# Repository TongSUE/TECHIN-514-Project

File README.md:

# TECHIN-514-Project : The Reality Color Dropper

## 1. Project Overview

**What it does:**
This project brings the digital "eyedropper" tool into real life. It consists of a pen-shaped device that scans the color of physical objects and a desktop station that displays the color data and the confidence level of the match. It helps designers capture colors from the real world instantly.

---

## 2. The Sensor Device (The Pen)

**Description:**
This is a handheld tool shaped like a marker pen. It utilizes a custom split-PCB architecture to fit the slim form factor. When the user finds a color, they press the button; the device reads the RGB value while blocking outside light and sends the data wirelessly to the base station.

**Key Components & Part Numbers:**

* **Controller: Seeed Studio XIAO ESP32C3**
    This thumb-sized microcontroller is selected for its compact footprint and built-in ESP-NOW capabilities. It fits perfectly inside the pen shaft.

* **Sensor Architecture: Split Custom PCB**
    To accommodate the pen's geometry, the circuit is split into two boards connected by a **1x4 Pin Header**:
    1.  **Main Board:** Vertically mounted inside the pen. Houses the MCU, battery pads, and switch.
    2.  **Sensor Tip:** A circular PCB mounted horizontally at the tip. Houses the **TCS34725 Sensor** and **LEDs** to ensure the sensor faces the paper perpendicularly.

* **Input: Tactile Button**
    Acts as a "shutter" trigger.

* **Power: Li-Po Battery (AAA size)**
    A cylindrical/prismatic lithium battery that connects to the motherboard via a battery holder.

* **Power Switch: Slide Switch**
    A side-mounted switch to cut off power completely.

---

## 3. The Display Device (The Base)

**Description:**
This is a desktop base that receives the color data. It features an OLED screen for data readout, a stepper motor gauge for visual feedback on accuracy, and a large LED for color reproduction.

**Key Components & Part Numbers:**

* **Controller: Seeed Studio XIAO ESP32C3**
    The base station uses the exact same controller as the pen. This unified architecture simplifies the codebase and BOM.

* **Display: 0.96" OLED Screen (SSD1306 Driver)**
    Displays the Hex/RGB codes via I2C interface.

* **Color Output: RGB LED**
    A programmable NeoPixel LED to visually visually recreate the scanned color.

* **Motor: x27_168 Stepper Motor**
    Indicates the "Confidence Level" (Euclidean distance) of the color match.

* **Power: 18650 Li-Ion Battery**
    Provides long-lasting power, boosted to 5V for the motor and LEDs.

---

## 4. System Logic & Communication

**Communication Method:**
The devices talk to each other using **ESP-NOW**.
* It is a peer-to-peer protocol (low latency).
* It does not require a router or Wi-Fi pairing.

**Workflow:**

1.  **Trigger:** User clicks the pen button.
2.  **Sensing:** The TCS34725 sensor (on the Daughterboard) reads the Raw RGB data.
3.  **Sending:** The Pen (XIAO ESP32C3) processes the data and sends it via ESP-NOW.
4.  **Receiving:** The Base (XIAO ESP32C3) receives the packet.
5.  **Processing (DSP/ML):** The Base calculates the **Euclidean Distance** between the scanned color and a stored color library (KNN algorithm).
6.  **Output:**
    * The **OLED** shows the color code.
    * The **Neopixel LED** lights up in that color.
    * The **Stepper Motor** moves the needle to show the confidence level.

---

# Electrical Schematics & PCB Layout

## Custom PCB Design
The pen utilizes a custom **Split-PCB Design** to manage the directional requirements of the sensor.

The split-PCB architecture is implemented to allow the sensor to sit perpendicular to the scanning surface for accurate readings, while the main controller fits vertically within the narrow pen shaft.

* **Connection:** The Main Board and Sensor Tip are linked via a flexible **1x5 Connector** carrying 3.3V, GND, SDA, SCL, and LED Control.
* **Power:** The battery connects to the tail of the Main Board via a **1x2 Connector**.

### **Custom PCB Screenshots**
- Sensing - Sensor Tip

- Sensing - Main Board

- Display

## Circuit Schematics

### **Sensing Device Schematic**
- Sensor Tip

- Main Board

### **Display Device Schematic**

---

# BOM

- [Sensing - Sensor Tip BOM](./schematics/Sensing_v3/sensor%20tip/sensor%20tip.csv)
- [Sensing - Main Board BOM](./schematics/Sensing_v2/sensor%20main%20board.csv)
- [Display BOM](./schematics/Display_v2/Display_v2.csv)

---

# Battery Estimate
- [Simple Power Model (Google Doc)](https://docs.google.com/spreadsheets/d/19ngwSyrM9dyAIHHAB65ps8SqUUKRAjS5MIs19pbbb7s/edit?usp=sharing)

---

# Enclosure Design
- [Enclosure Design](./enclosure/)

### Sensing Device

### Display Device

---

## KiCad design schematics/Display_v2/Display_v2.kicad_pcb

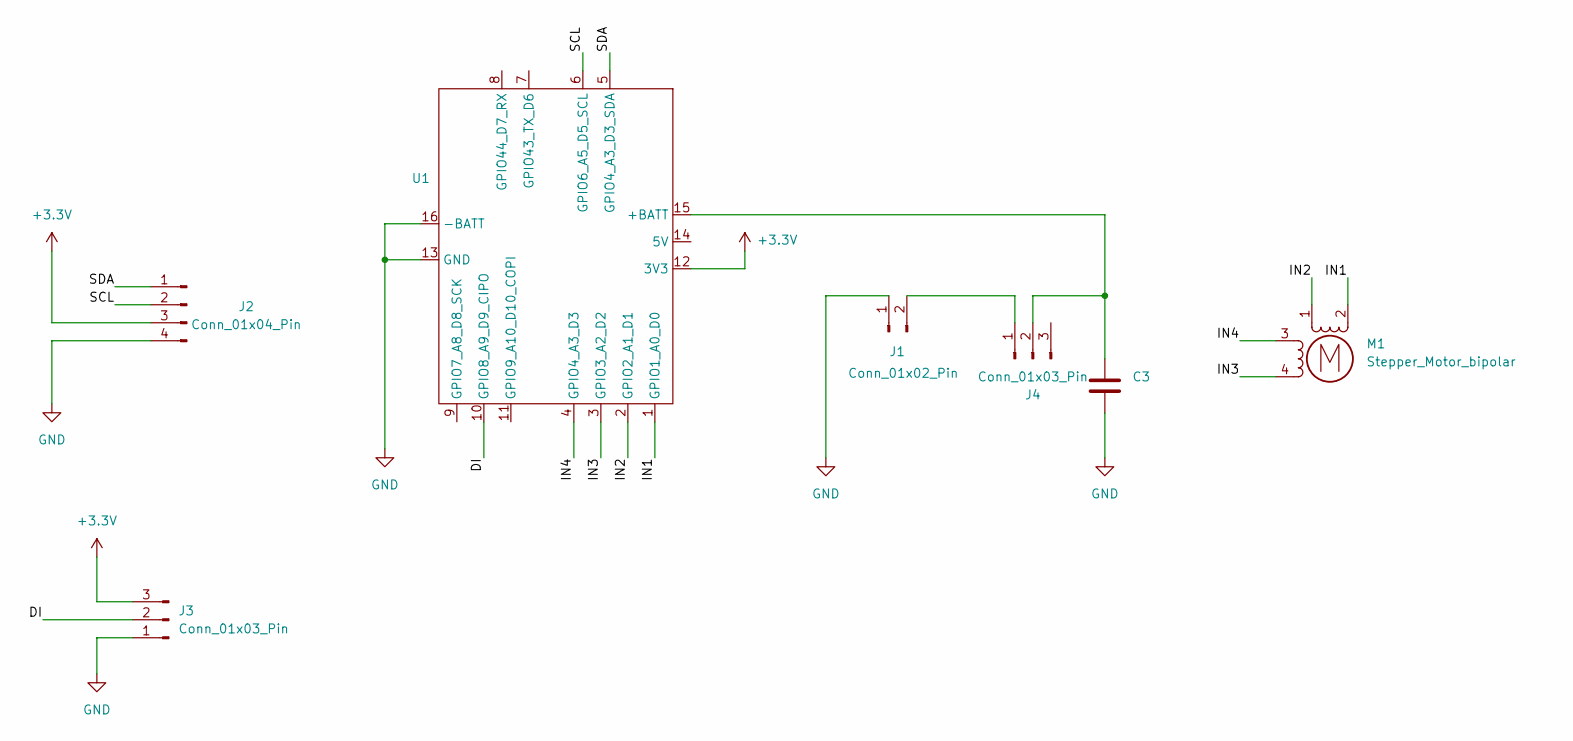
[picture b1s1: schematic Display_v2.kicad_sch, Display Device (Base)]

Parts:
C3: 22uF; C_0603_1608Metric_Pad1.08x0.95mm_HandSolder
J1: Conn_01x02_Pin; PinSocket_1x02_P2.54mm_Vertical
J2: Conn_01x04_Pin; PinSocket_1x04_P2.54mm_Vertical
J3, J4: Conn_01x03_Pin; PinSocket_1x03_P2.54mm_Vertical
M1: Stepper_Motor_bipolar; x27_stepper_two_holes
U1: XIAO_ESP32

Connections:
+3.3V: J2.3, J3.3, U1.12 (3V3)
/DI: J3.2, U1.10 (GPIO8_A9_D9_CIPO)
/IN1: M1.2 (-), U1.1 (GPIO1_A0_D0)
/IN2: M1.1, U1.2 (GPIO2_A1_D1)
/IN3: M1.4, U1.3 (GPIO3_A2_D2)
/IN4: M1.3, U1.4 (GPIO4_A3_D3)
/SCL: J2.2, U1.6 (GPIO6_A5_D5_SCL)
/SDA: J2.1, U1.5 (GPIO4_A3_D3_SDA)
GND: C3.2, J1.1, J2.4, J3.1, U1.13 (GND), U1.16 (-BATT)
unnamed: J1.2, J4.1
unnamed: C3.1, J4.2, U1.15 (+BATT)

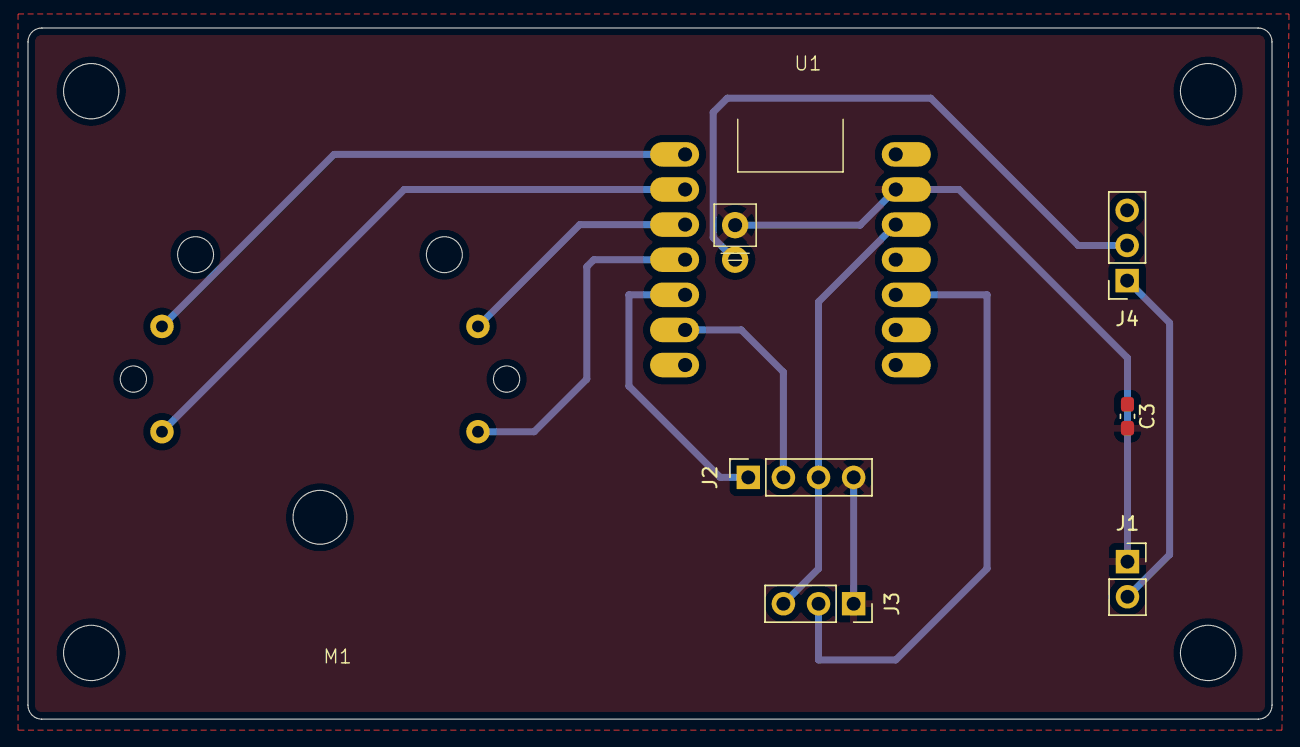
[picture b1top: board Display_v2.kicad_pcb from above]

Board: 2 copper layers, 90.0 x 50.0 mm, 7 parts (0 on the bottom side), 11 nets.

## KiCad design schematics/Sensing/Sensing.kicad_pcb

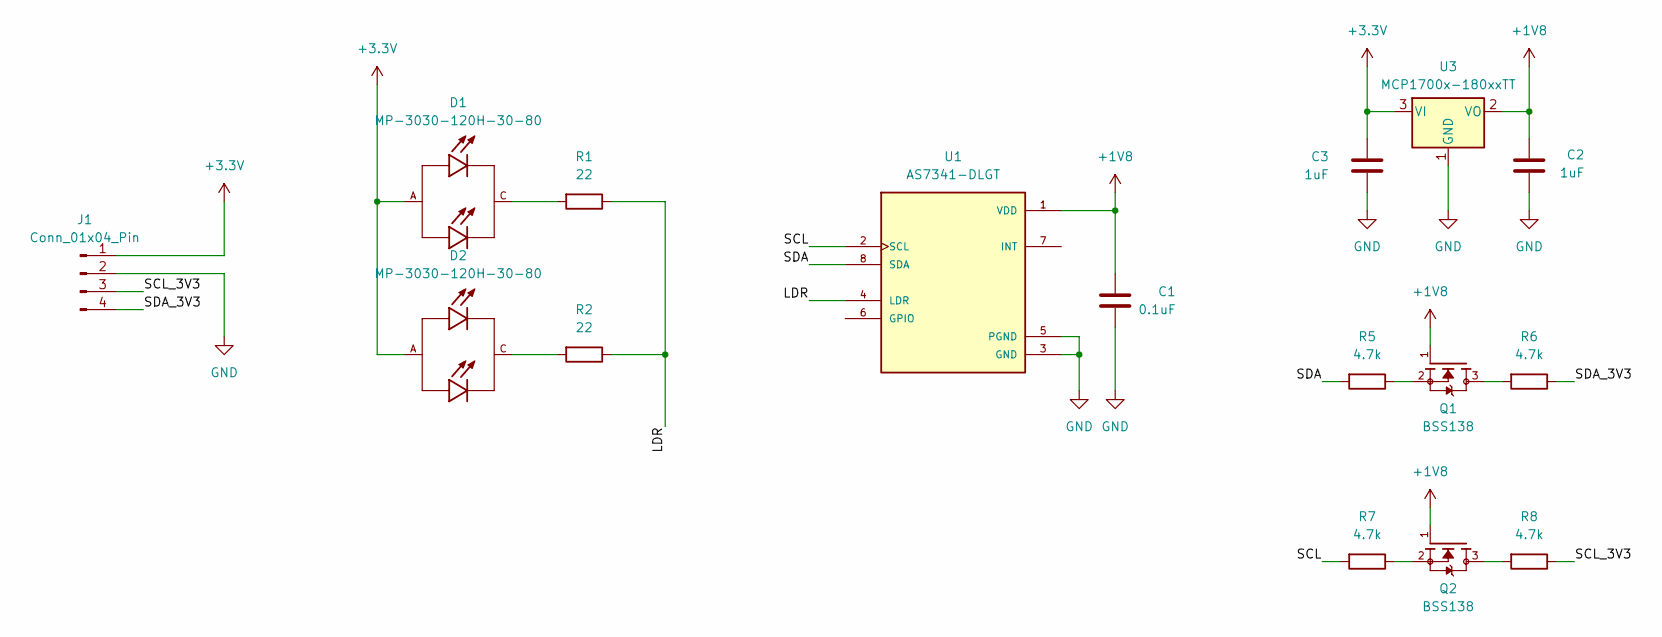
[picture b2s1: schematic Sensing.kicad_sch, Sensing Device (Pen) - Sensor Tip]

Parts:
C1: 0.1uF; C_0603_1608Metric_Pad1.08x0.95mm_HandSolder
C2, C3: 1uF; C_0603_1608Metric_Pad1.08x0.95mm_HandSolder
D1, D2: MP-3030-120H-30-80; LED_MP-3030-120H-30-80; PARTREV Rev 03
J1: Conn_01x04_Pin; PinSocket_1x04_P2.54mm_Vertical
Q1, Q2: BSS138; SOT-23_3L_ONS; PARTREV 30 Jan 2018
R1, R2: 22; R_0603_1608Metric_Pad0.98x0.95mm_HandSolder
R5, R6, R7, R8: 4.7k; R_0603_1608Metric_Pad0.98x0.95mm_HandSolder
U1: AS7341-DLGT; SON8_AS7341-DLGM_AMS; PARTREV V3
U3: MCP1700x-180xxTT; SOT-23

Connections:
+1V8: C1.1, C2.1, Q1.1, Q2.1, U1.1 (VDD), U3.2 (VO)
+3.3V: C3.1, D1.A, D2.A, J1.1, U3.3 (VI)
/LDR: R1.1, R2.1, U1.4 (LDR)
/SCL: R7.2, U1.2 (SCL)
/SCL_3V3: J1.3, R8.1
/SDA: R5.2, U1.8 (SDA)
/SDA_3V3: J1.4, R6.1
GND: C1.2, C2.2, C3.2, J1.2, U1.3 (GND), U1.5 (PGND), U3.1 (GND)
unnamed: D1.C, R1.2
unnamed: D2.C, R2.2
unnamed: Q1.2, R5.1
unnamed: Q1.3, R6.2
unnamed: Q2.2, R7.1
unnamed: Q2.3, R8.2

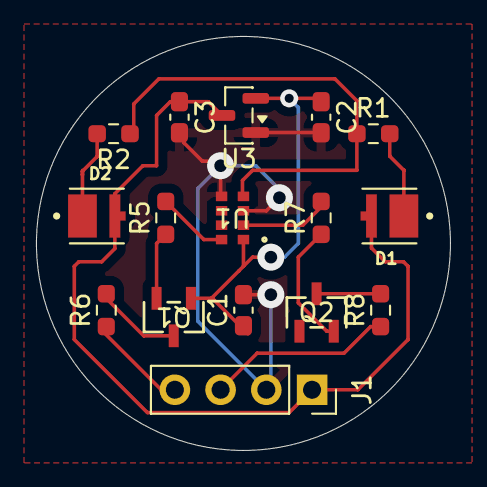
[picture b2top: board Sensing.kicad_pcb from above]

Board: 2 copper layers, 23.0 x 23.0 mm, 16 parts (0 on the bottom side), 14 nets.

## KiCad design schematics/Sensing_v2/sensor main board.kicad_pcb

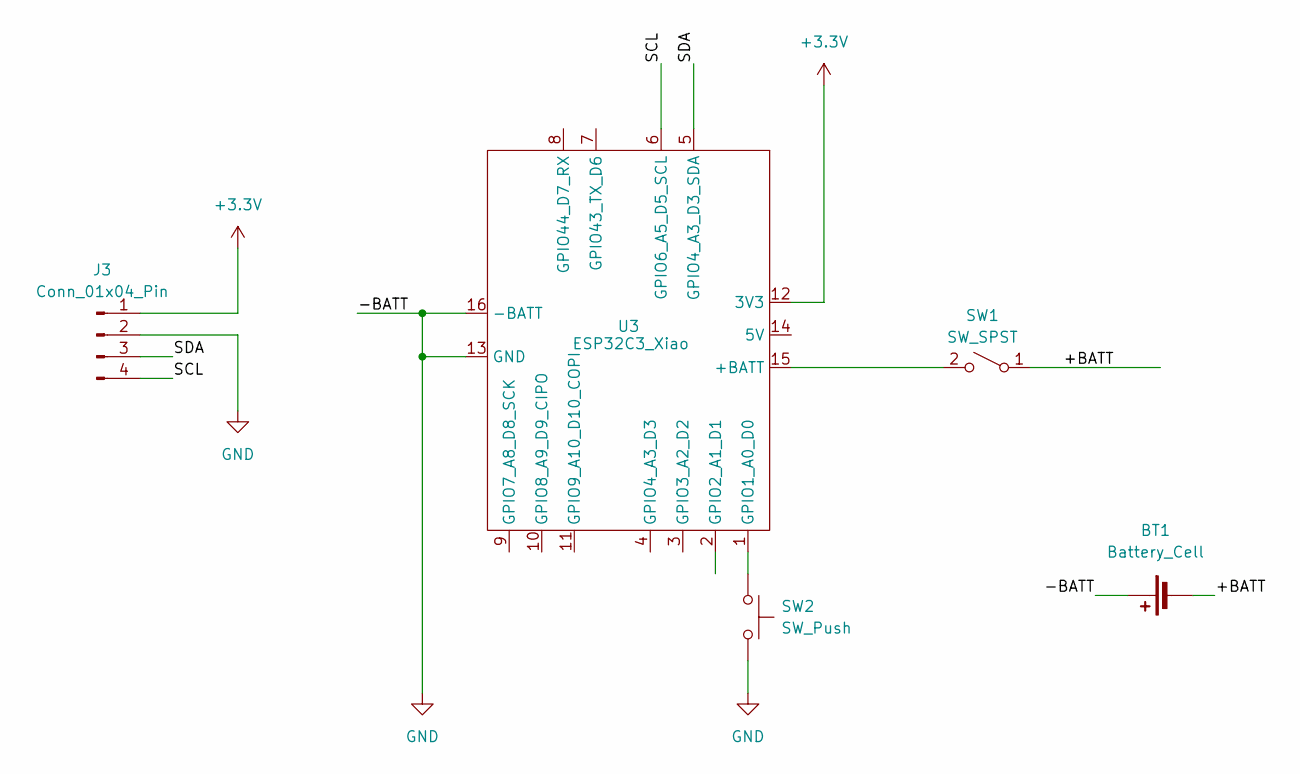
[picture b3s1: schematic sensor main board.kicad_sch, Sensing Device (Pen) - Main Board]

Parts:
BT1: Battery_Cell; BatteryHolder_Keystone_2466_1xAAA
J3: Conn_01x04_Pin; PinSocket_1x04_P2.54mm_Vertical
SW1: SW_SPST; PinSocket_1x02_P2.54mm_Vertical
SW2: SW_Push; SW_MEC_5GSH9
U3: ESP32C3_Xiao; XIAO_ESP32

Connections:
+3.3V: J3.1, U3.12 (3V3)
/+BATT: BT1.2 (-), SW1.1 (A)
/SCL: J3.4, U3.6 (GPIO6_A5_D5_SCL)
/SDA: J3.3, U3.5 (GPIO4_A3_D3_SDA)
GND: BT1.1 (+), J3.2, SW2.2, U3.13 (GND), U3.16 (-BATT)
unnamed: SW1.2 (B), U3.15 (+BATT)
unnamed: SW2.1, U3.1 (GPIO1_A0_D0)

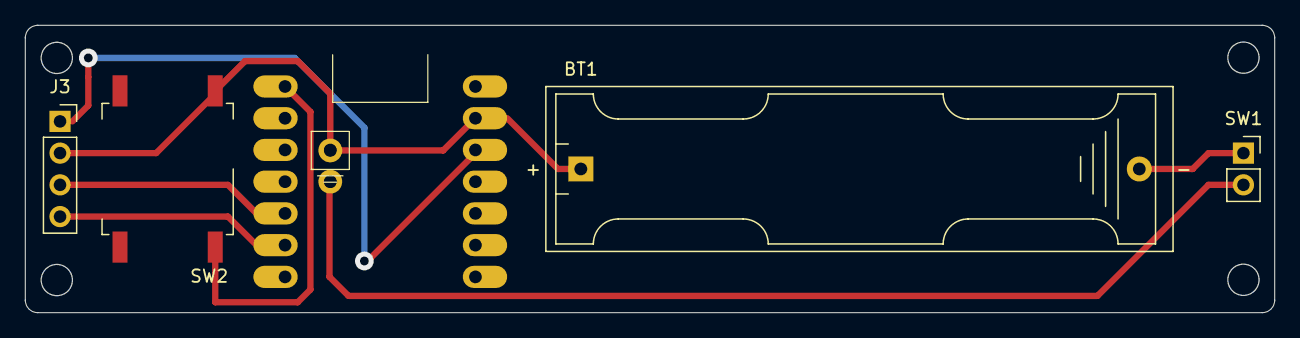
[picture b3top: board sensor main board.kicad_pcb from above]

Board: 2 copper layers, 99.9 x 23.0 mm, 5 parts (0 on the bottom side), 7 nets.

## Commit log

2026-01-20 System Architecture with Diagram (HW+SW)
2026-01-27 Update KiCAD
2026-02-03 Update for PCB design review
2026-02-03 README
2026-02-05 Custom PCB Design
2026-02-07 Update Battery Estimate
2026-03-01 Update PCB and Enclosure Designs
2026-03-02 Update Code and Enclosure Screenshots
2026-03-14 Update code
